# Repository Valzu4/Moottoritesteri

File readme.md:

# Motor tester
This project is a motor tester for testing vending machine motors for various different fault types.

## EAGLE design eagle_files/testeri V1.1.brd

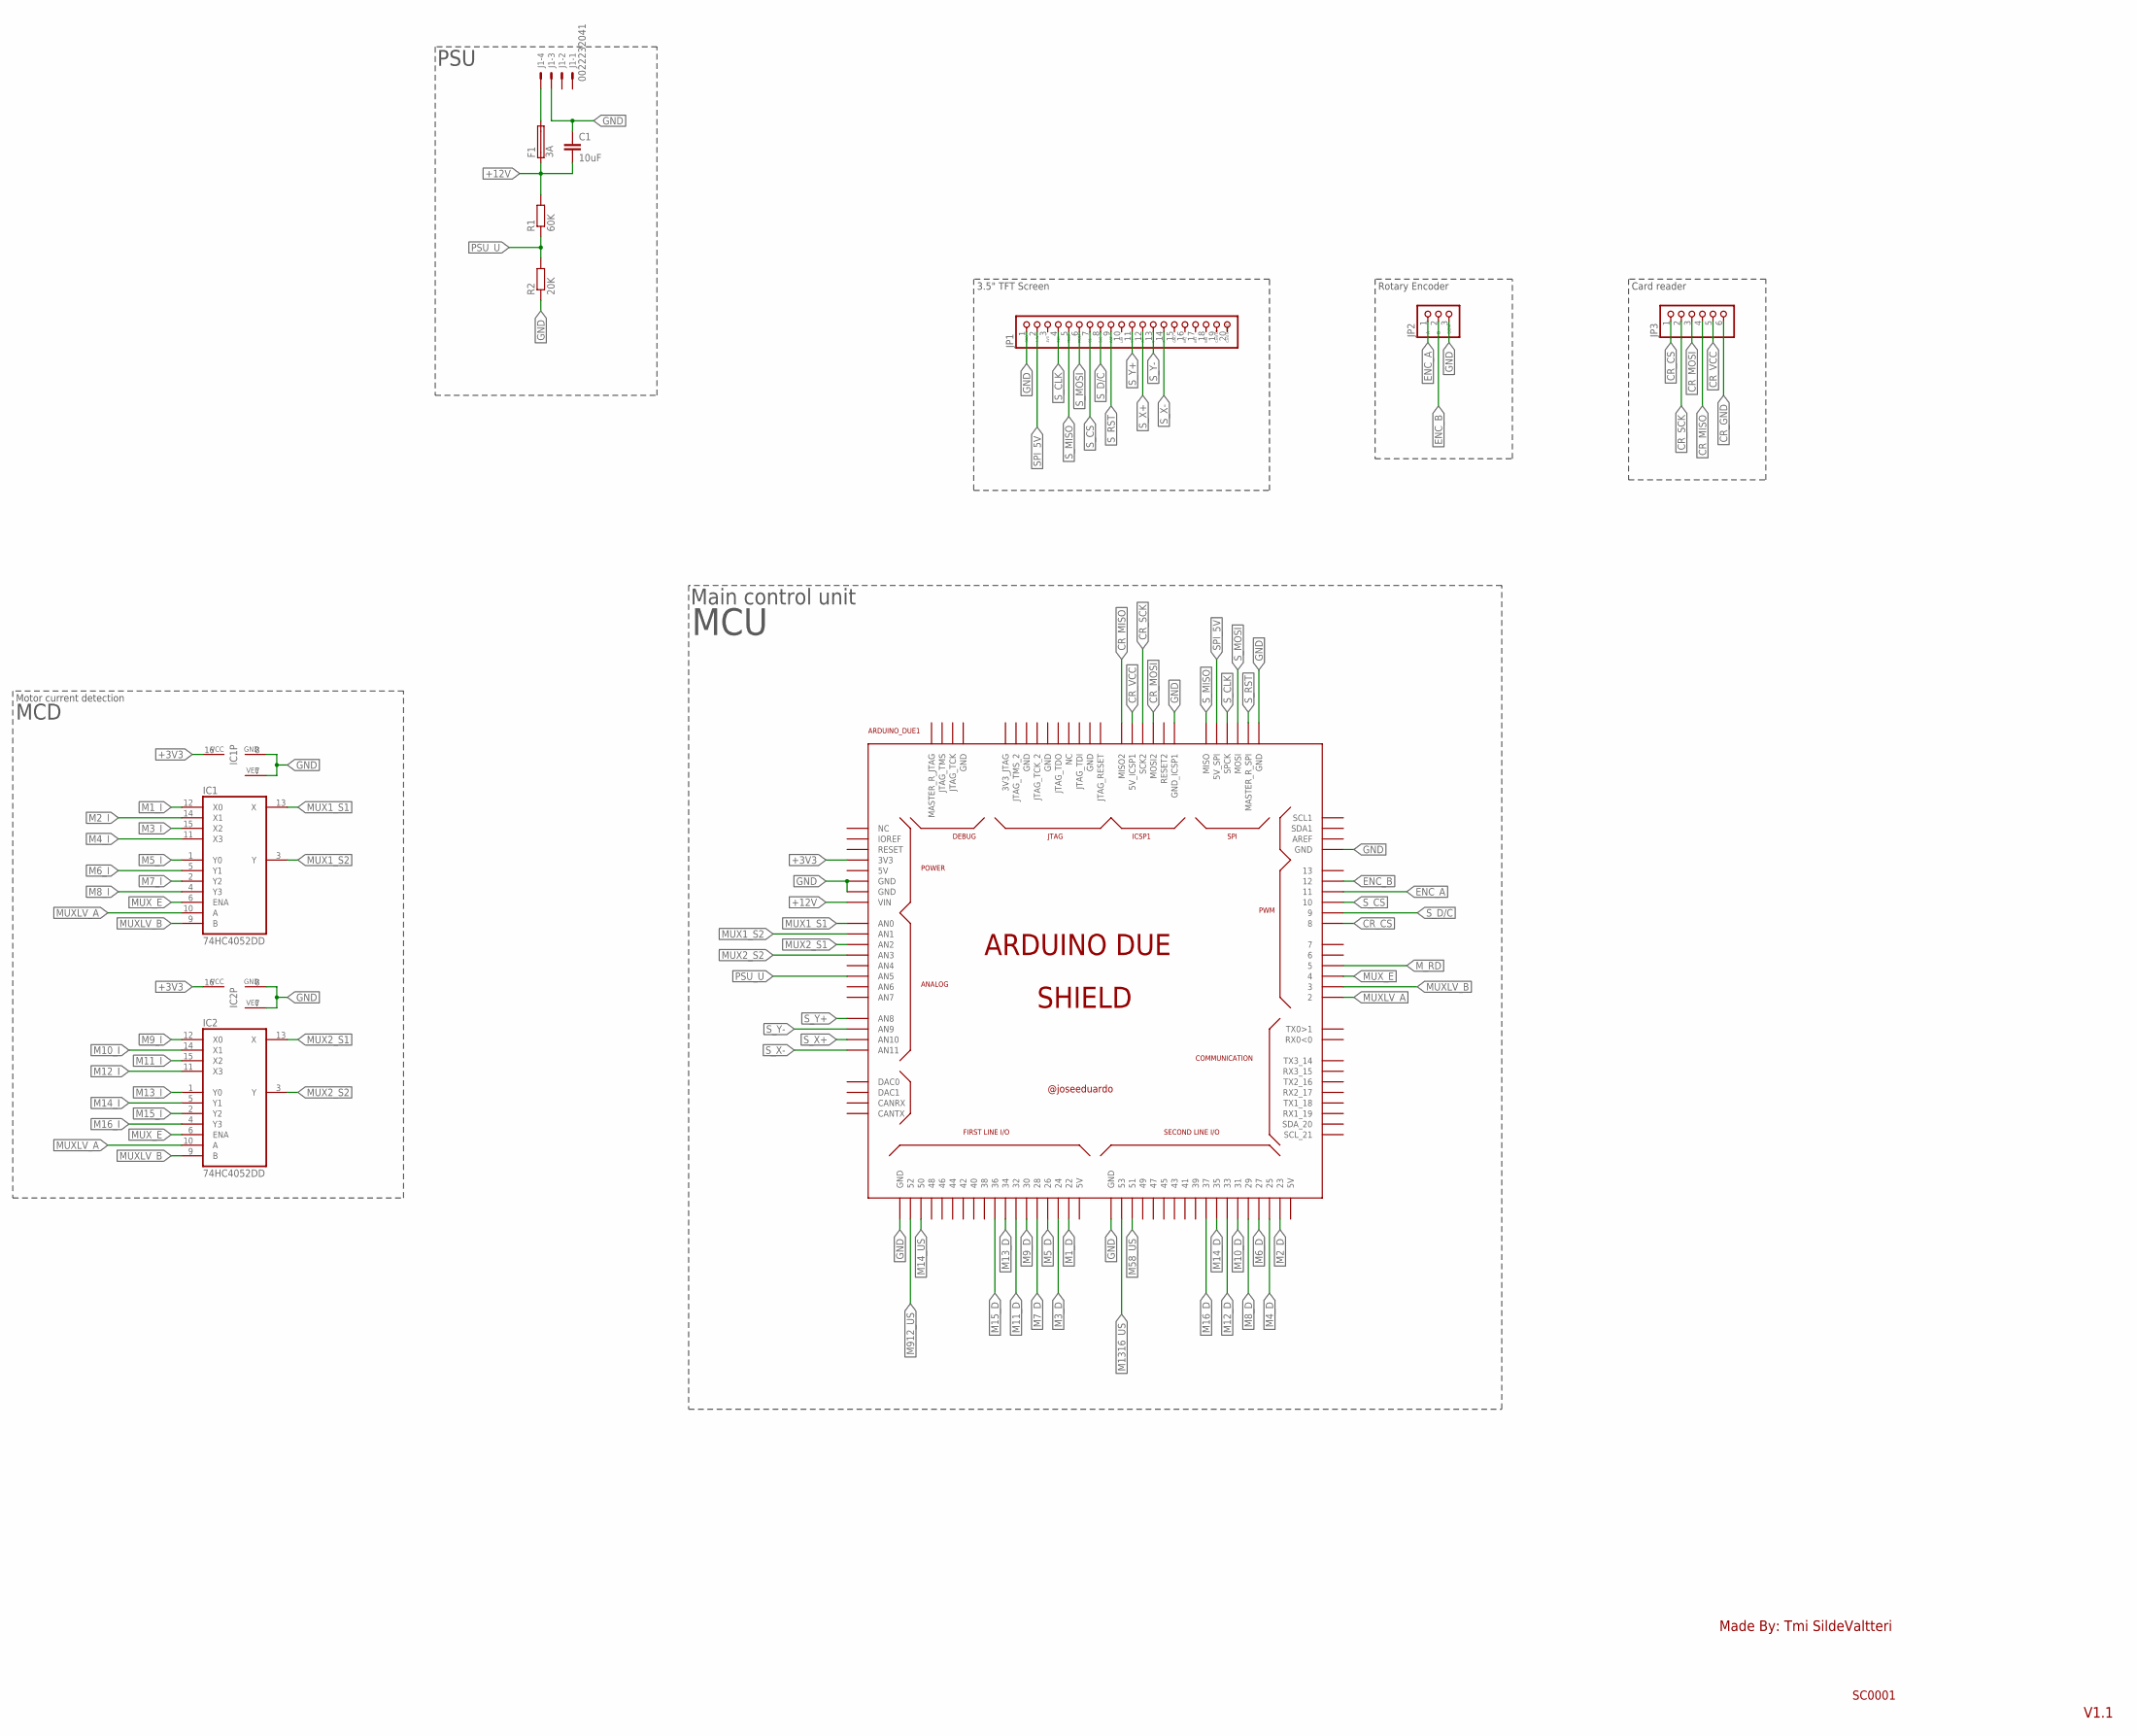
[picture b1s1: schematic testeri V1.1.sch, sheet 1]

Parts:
ARDUINO_DUE1: ARDUINO_DUE_SHIELD
C1: 10uF; C3216
F1: 3A; SH22,5
IC1, IC2: 74HC4052DD; SO16
J1: 0022232041; 6410-04
JP1: PINHD-1X20; 1X20
JP2: PINHD-1X3; 1X03
JP3: PINHD-1X6; 1X06
R1: 60K; R3216W
R2: 20K; R3216W

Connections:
+3V3: ARDUINO_DUE1.3V3, IC1.16 (VCC), IC2.16 (VCC); also elsewhere on the board
+12V: ARDUINO_DUE1.VIN, C1.2, F1.1, R1.2; also elsewhere on the board
CR_CS: ARDUINO_DUE1.8, JP3.1
CR_GND: JP3.6
CR_MISO: ARDUINO_DUE1.MISO2, JP3.4
CR_MOSI: ARDUINO_DUE1.MOSI2, JP3.3
CR_SCK: ARDUINO_DUE1.SCK2, JP3.2
CR_VCC: ARDUINO_DUE1.5V_ICSP1, JP3.5
ENC_A: ARDUINO_DUE1.11, JP2.1
ENC_B: ARDUINO_DUE1.12, JP2.2
GND: ARDUINO_DUE1.GND, ARDUINO_DUE1.GND_1 (GND), ARDUINO_DUE1.GND_2 (GND), ARDUINO_DUE1.GND_3 (GND), ARDUINO_DUE1.GND_4 (GND), ARDUINO_DUE1.GND_5 (GND), ARDUINO_DUE1.GND_ICSP1, C1.1, IC1.7 (VEE), IC1.8 (GND), IC2.7 (VEE), IC2.8 (GND), J1.3, JP1.1, JP2.3, R2.1; also elsewhere on the board
M1_D: ARDUINO_DUE1.22; also elsewhere on the board
M1_I: IC1.12 (X0); also elsewhere on the board
M2_D: ARDUINO_DUE1.23; also elsewhere on the board
M2_I: IC1.14 (X1); also elsewhere on the board
M3_D: ARDUINO_DUE1.24; also elsewhere on the board
M3_I: IC1.15 (X2); also elsewhere on the board
M4_D: ARDUINO_DUE1.25; also elsewhere on the board
M4_I: IC1.11 (X3); also elsewhere on the board
M5_D: ARDUINO_DUE1.26; also elsewhere on the board
M5_I: IC1.1 (Y0); also elsewhere on the board
M6_D: ARDUINO_DUE1.27; also elsewhere on the board
M6_I: IC1.5 (Y1); also elsewhere on the board
M7_D: ARDUINO_DUE1.28; also elsewhere on the board
M7_I: IC1.2 (Y2); also elsewhere on the board
M8_D: ARDUINO_DUE1.29; also elsewhere on the board
M8_I: IC1.4 (Y3); also elsewhere on the board
M9_D: ARDUINO_DUE1.30; also elsewhere on the board
M9_I: IC2.12 (X0); also elsewhere on the board
M10_D: ARDUINO_DUE1.31; also elsewhere on the board
M10_I: IC2.14 (X1); also elsewhere on the board
M11_D: ARDUINO_DUE1.32; also elsewhere on the board
M11_I: IC2.15 (X2); also elsewhere on the board
M12_D: ARDUINO_DUE1.33; also elsewhere on the board
M12_I: IC2.11 (X3); also elsewhere on the board
M13_D: ARDUINO_DUE1.34; also elsewhere on the board
M13_I: IC2.1 (Y0); also elsewhere on the board
M14_D: ARDUINO_DUE1.35; also elsewhere on the board
M14_I: IC2.5 (Y1); also elsewhere on the board
M14_US: ARDUINO_DUE1.50; also elsewhere on the board
M15_D: ARDUINO_DUE1.36; also elsewhere on the board
M15_I: IC2.2 (Y2); also elsewhere on the board
M16_D: ARDUINO_DUE1.37; also elsewhere on the board
M16_I: IC2.4 (Y3); also elsewhere on the board
M58_US: ARDUINO_DUE1.51; also elsewhere on the board
M912_US: ARDUINO_DUE1.52; also elsewhere on the board
M1316_US: ARDUINO_DUE1.53; also elsewhere on the board
MUX1_S1: ARDUINO_DUE1.A0 (AN0), IC1.13 (X)
MUX1_S2: ARDUINO_DUE1.A1 (AN1), IC1.3 (Y)
MUX2_S1: ARDUINO_DUE1.A2 (AN2), IC2.13 (X)
MUX2_S2: ARDUINO_DUE1.A3 (AN3), IC2.3 (Y)
MUXLV_A: ARDUINO_DUE1.2, IC1.10 (A), IC2.10 (A)
MUXLV_B: ARDUINO_DUE1.3, IC1.9 (B), IC2.9 (B)
MUX_E: ARDUINO_DUE1.4, IC1.6 (ENA), IC2.6 (ENA)
M_RD: ARDUINO_DUE1.5; also elsewhere on the board
unnamed: F1.2, J1.4
PSU_U: ARDUINO_DUE1.A5 (AN5), R1.1, R2.2
SPI_5V: ARDUINO_DUE1.5V_2 (5V_SPI), JP1.2
S_CLK: ARDUINO_DUE1.SPCK, JP1.4
S_CS: ARDUINO_DUE1.10, JP1.7
S_D/C: ARDUINO_DUE1.9, JP1.8
S_MISO: ARDUINO_DUE1.MISO, JP1.5
S_MOSI: ARDUINO_DUE1.MOSI, JP1.6
S_RST: ARDUINO_DUE1.MASTER_RESET_SPI (MASTER_R_SPI), JP1.9
S_X+: ARDUINO_DUE1.A10 (AN10), JP1.12
S_X-: ARDUINO_DUE1.A11 (AN11), JP1.14
S_Y+: ARDUINO_DUE1.A8 (AN8), JP1.11
S_Y-: ARDUINO_DUE1.A9 (AN9), JP1.13

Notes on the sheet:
Made By: Tmi SildeValtteri
SC0001
V1.1
COM
Rotary Encoder
3.5" TFT Screen
PSU
Motor current detection
Main control unit
MCU
MCD
Card reader

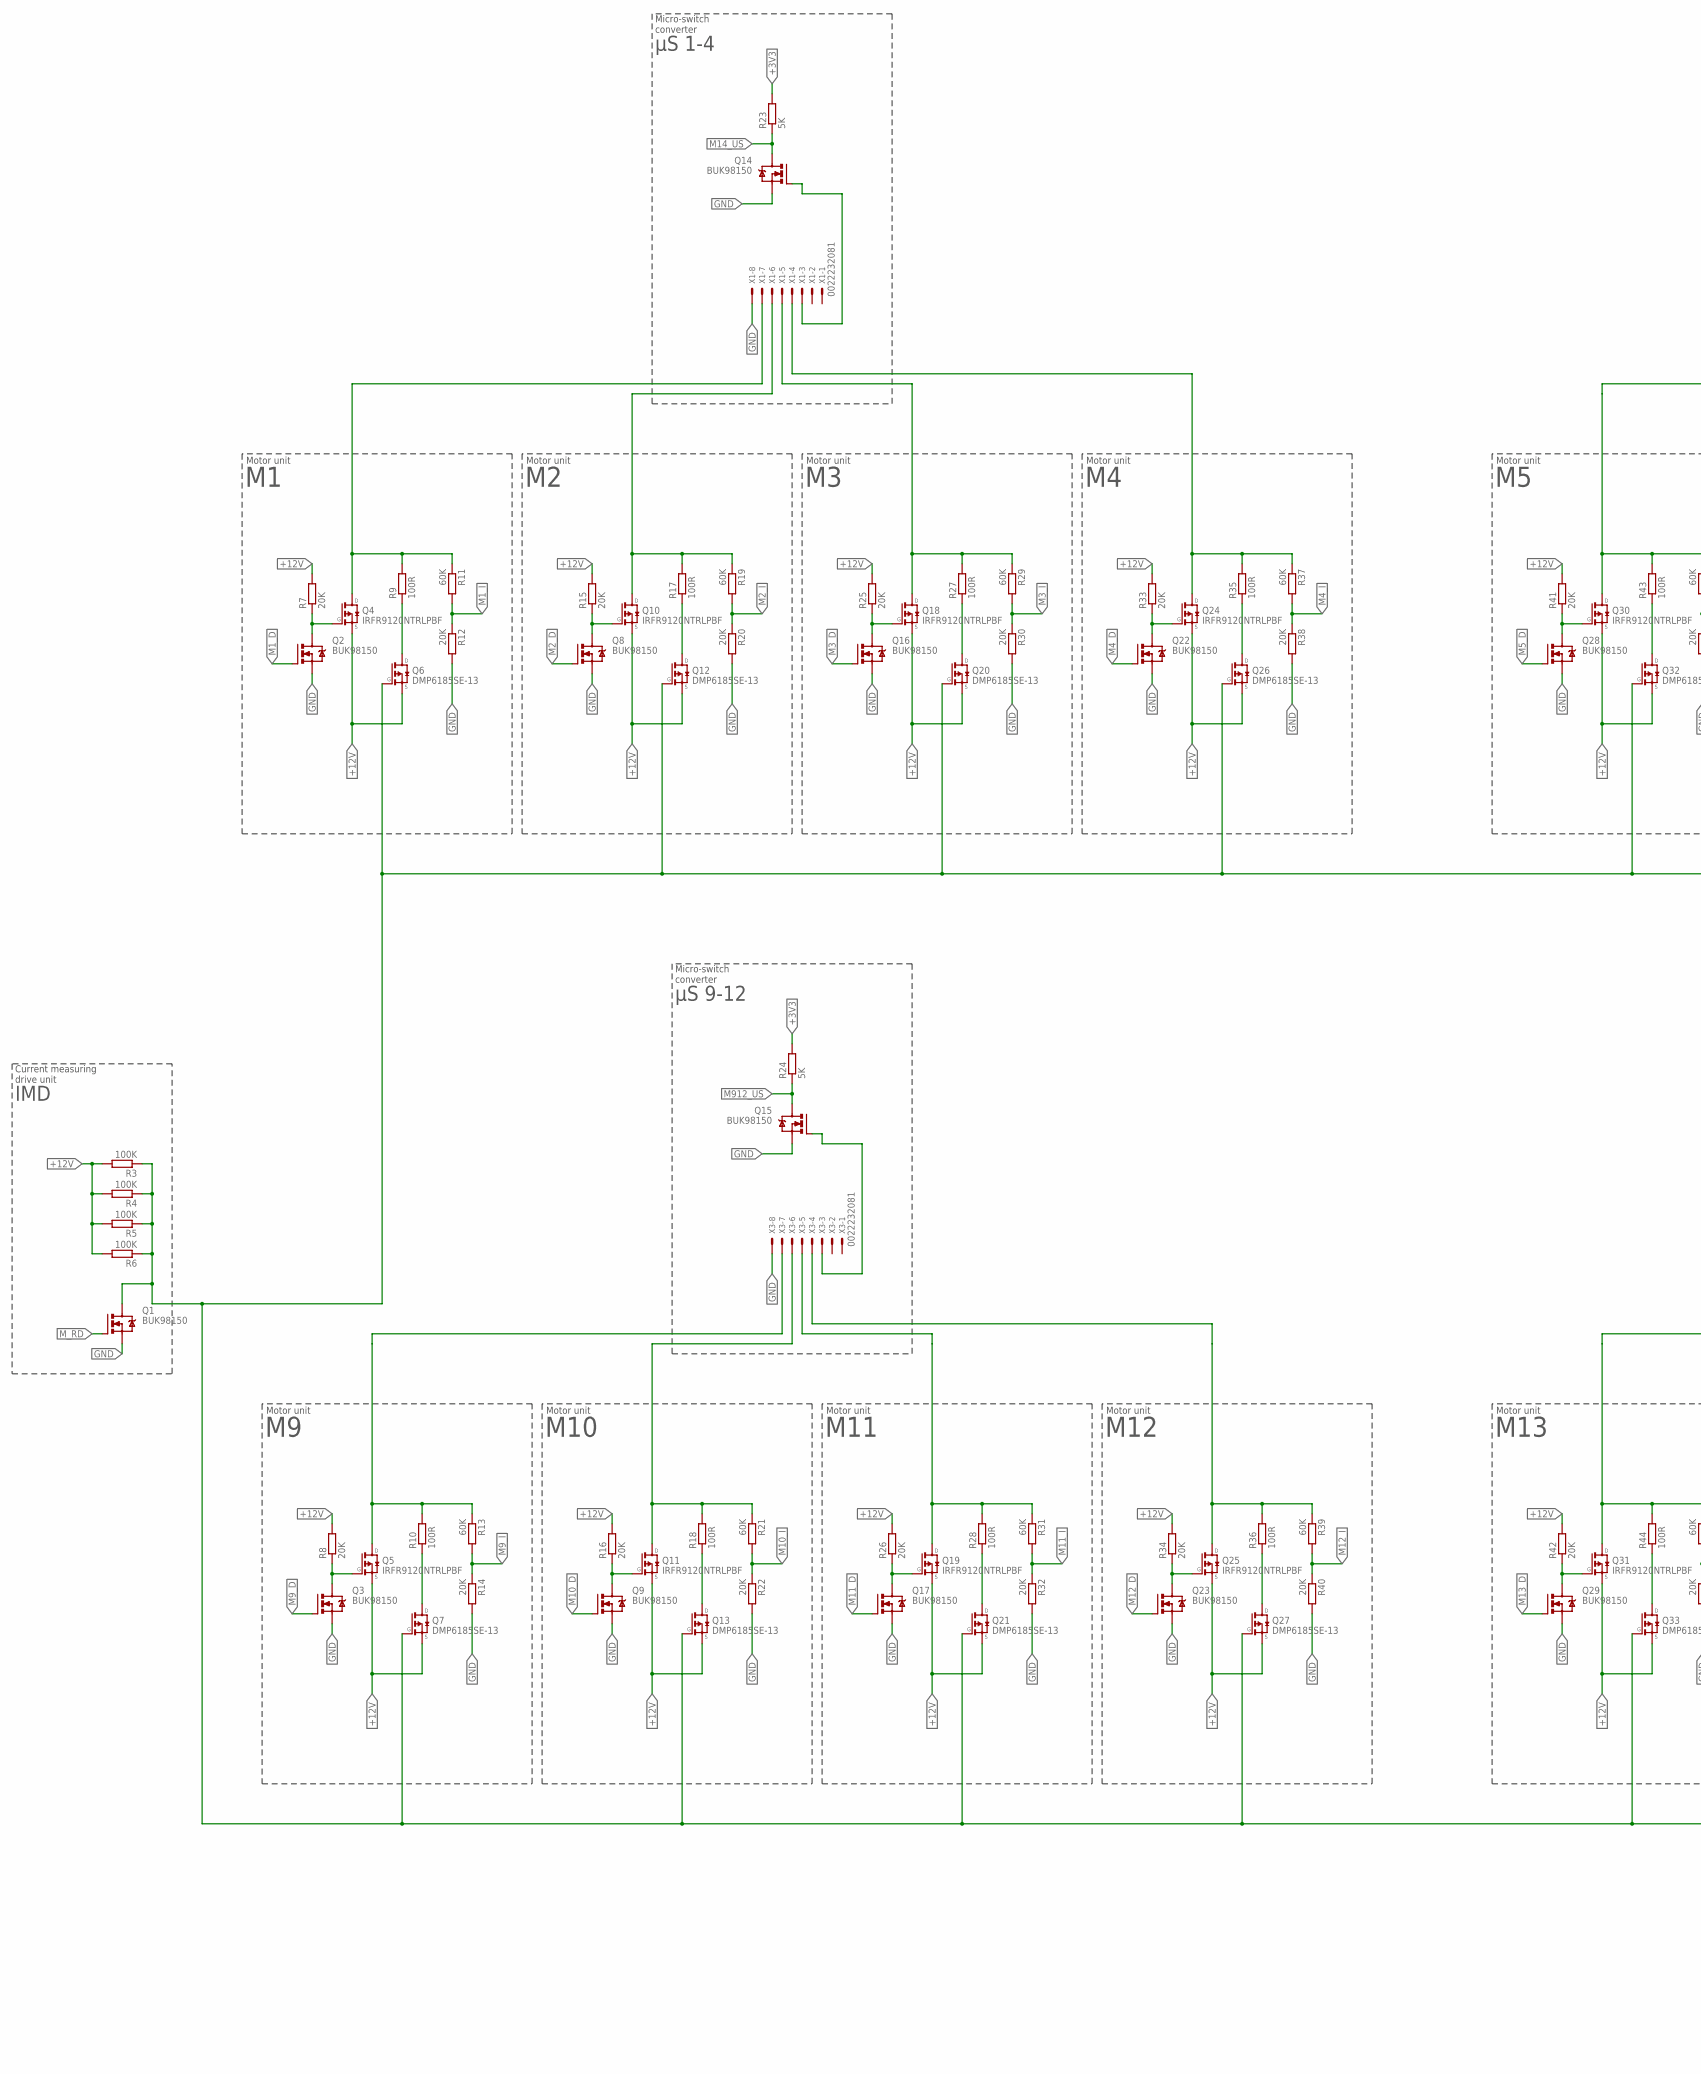
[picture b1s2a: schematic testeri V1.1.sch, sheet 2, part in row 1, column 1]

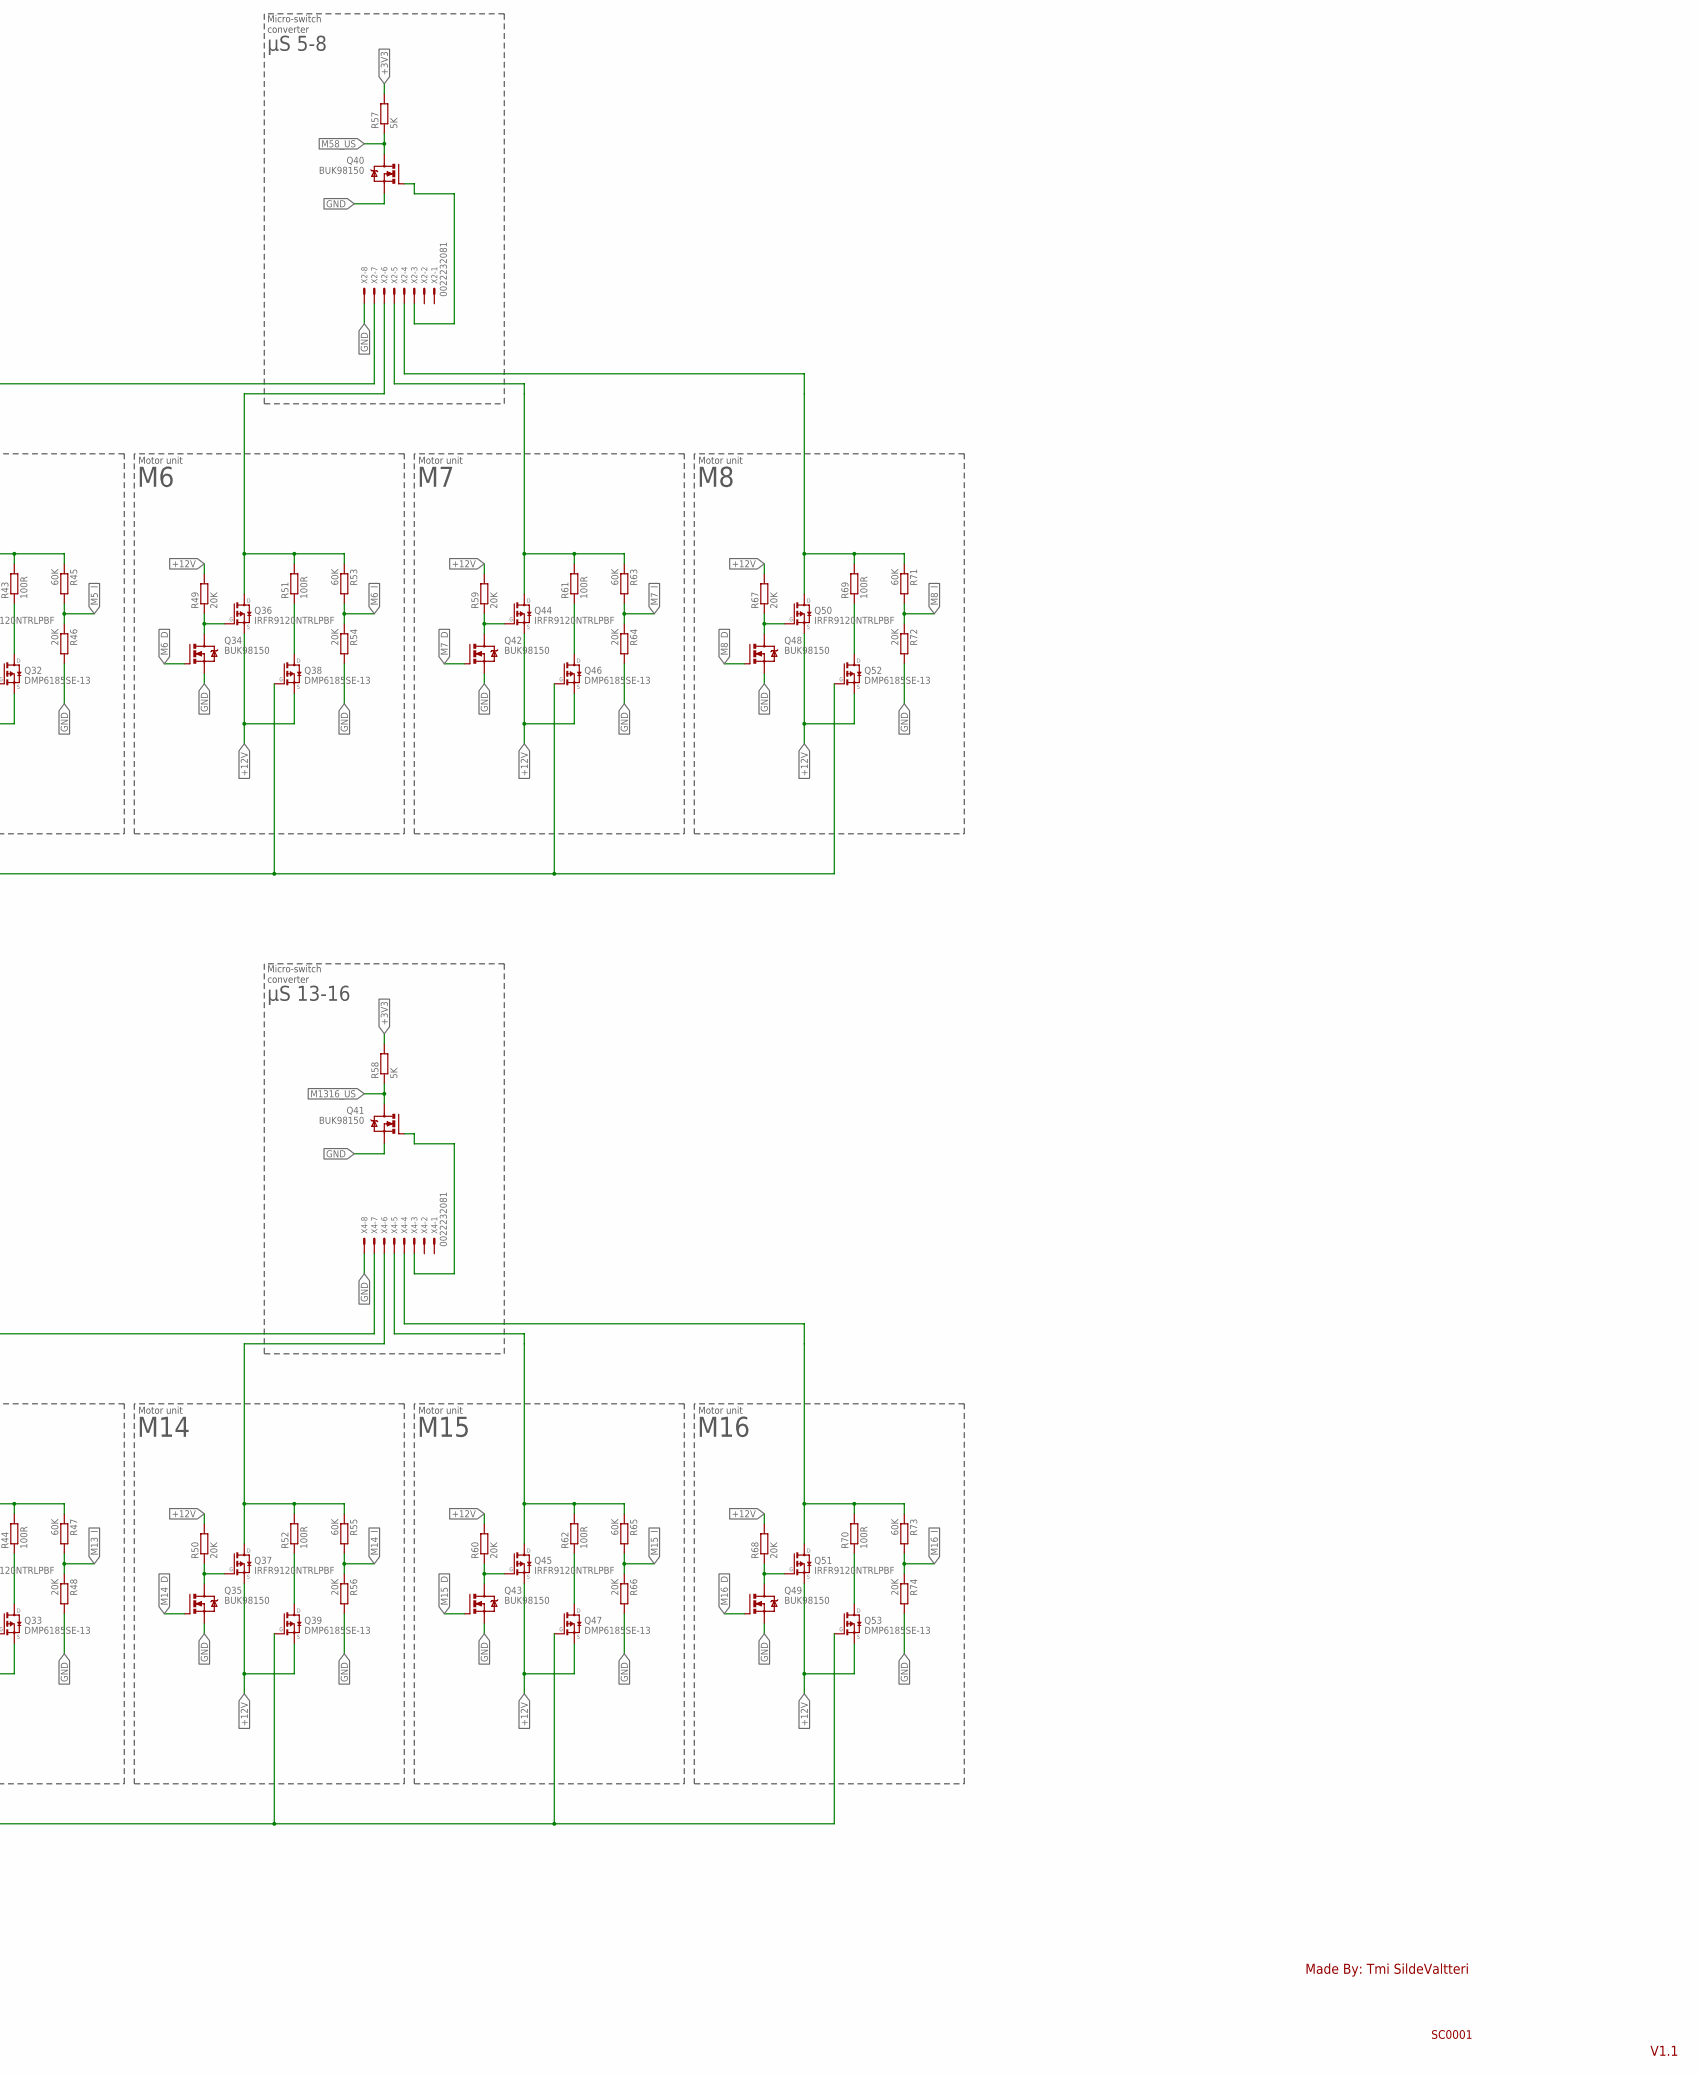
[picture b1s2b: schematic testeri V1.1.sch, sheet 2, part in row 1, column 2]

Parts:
Q1, Q2, Q3, Q8, Q9, Q14, Q15, Q16, Q17, Q22, Q23, Q28, Q29, Q34, Q35, Q40, Q41, Q42, Q43, Q48, Q49: BUK98150; SOT223
Q4, Q5, Q10, Q11, Q18, Q19, Q24, Q25, Q30, Q31, Q36, Q37, Q44, Q45, Q50, Q51: IRFR9120NTRLPBF; D-PAK_TO252AA
Q6, Q7, Q12, Q13, Q20, Q21, Q26, Q27, Q32, Q33, Q38, Q39, Q46, Q47, Q52, Q53: DMP6185SE-13; SOT223
R3, R4, R5, R6: 100K; R3216W
R7, R8, R12, R14, R15, R16, R20, R22, R25, R26, R30, R32, R33, R34, R38, R40, R41, R42, R46, R48, R49, R50, R54, R56, R59, R60, R64, R66, R67, R68, R72, R74: 20K; R3216W
R9, R10, R17, R18, R27, R28, R35, R36, R43, R44, R51, R52, R61, R62, R69, R70: 100R; 0411/15
R11, R13, R19, R21, R29, R31, R37, R39, R45, R47, R53, R55, R63, R65, R71, R73: 60K; R3216W
R23, R24, R57, R58: 5K; R3216W
X1, X2, X3, X4: 0022232081; 22-23-2081

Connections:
+3V3: R23.2, R24.2, R57.2, R58.2; also elsewhere on the board
+12V: Q4.3 (S), Q5.3 (S), Q6.3 (S), Q7.3 (S), Q10.3 (S), Q11.3 (S), Q12.3 (S), Q13.3 (S), Q18.3 (S), Q19.3 (S), Q20.3 (S), Q21.3 (S), Q24.3 (S), Q25.3 (S), Q26.3 (S), Q27.3 (S), Q30.3 (S), Q31.3 (S), Q32.3 (S), Q33.3 (S), Q36.3 (S), Q37.3 (S), Q38.3 (S), Q39.3 (S), Q44.3 (S), Q45.3 (S), Q46.3 (S), Q47.3 (S), Q50.3 (S), Q51.3 (S), Q52.3 (S), Q53.3 (S), R3.2, R4.2, R5.2, R6.2, R7.2, R8.2, R15.2, R16.2, R25.2, R26.2, R33.2, R34.2, R41.2, R42.2, R49.2, R50.2, R59.2, R60.2, R67.2, R68.2; also elsewhere on the board
GND: Q1.3 (S), Q2.3 (S), Q3.3 (S), Q8.3 (S), Q9.3 (S), Q14.3 (S), Q15.3 (S), Q16.3 (S), Q17.3 (S), Q22.3 (S), Q23.3 (S), Q28.3 (S), Q29.3 (S), Q34.3 (S), Q35.3 (S), Q40.3 (S), Q41.3 (S), Q42.3 (S), Q43.3 (S), Q48.3 (S), Q49.3 (S), R12.2, R14.2, R20.2, R22.2, R30.2, R32.2, R38.2, R40.2, R46.2, R48.2, R54.2, R56.2, R64.2, R66.2, R72.2, R74.2, X1.8, X2.8, X3.8, X4.8; also elsewhere on the board
M1_D: Q2.1 (G); also elsewhere on the board
M1_I: R11.2, R12.1; also elsewhere on the board
M2_D: Q8.1 (G); also elsewhere on the board
M2_I: R19.2, R20.1; also elsewhere on the board
M3_D: Q16.1 (G); also elsewhere on the board
M3_I: R29.2, R30.1; also elsewhere on the board
M4_D: Q22.1 (G); also elsewhere on the board
M4_I: R37.2, R38.1; also elsewhere on the board
M5_D: Q28.1 (G); also elsewhere on the board
M5_I: R45.2, R46.1; also elsewhere on the board
M6_D: Q34.1 (G); also elsewhere on the board
M6_I: R53.2, R54.1; also elsewhere on the board
M7_D: Q42.1 (G); also elsewhere on the board
M7_I: R63.2, R64.1; also elsewhere on the board
M8_D: Q48.1 (G); also elsewhere on the board
M8_I: R71.2, R72.1; also elsewhere on the board
M9_D: Q3.1 (G); also elsewhere on the board
M9_I: R13.2, R14.1; also elsewhere on the board
M10_D: Q9.1 (G); also elsewhere on the board
M10_I: R21.2, R22.1; also elsewhere on the board
M11_D: Q17.1 (G); also elsewhere on the board
M11_I: R31.2, R32.1; also elsewhere on the board
M12_D: Q23.1 (G); also elsewhere on the board
M12_I: R39.2, R40.1; also elsewhere on the board
M13_D: Q29.1 (G); also elsewhere on the board
M13_I: R47.2, R48.1; also elsewhere on the board
M14_D: Q35.1 (G); also elsewhere on the board
M14_I: R55.2, R56.1; also elsewhere on the board
M14_US: Q14.2 (D), Q14.4 (D), R23.1; also elsewhere on the board
M15_D: Q43.1 (G); also elsewhere on the board
M15_I: R65.2, R66.1; also elsewhere on the board
M16_D: Q49.1 (G); also elsewhere on the board
M16_I: R73.2, R74.1; also elsewhere on the board
M58_US: Q40.2 (D), Q40.4 (D), R57.1; also elsewhere on the board
M912_US: Q15.2 (D), Q15.4 (D), R24.1; also elsewhere on the board
M1316_US: Q41.2 (D), Q41.4 (D), R58.1; also elsewhere on the board
M_RD: Q1.1 (G); also elsewhere on the board
unnamed: Q8.2 (D), Q8.4 (D), Q10.1 (G), R15.1
unnamed: Q14.1 (G), X1.3
unnamed: Q10.4 (D), R17.2, R19.1, X1.6
unnamed: Q1.2 (D), Q1.4 (D), Q6.1 (G), Q7.1 (G), Q12.1 (G), Q13.1 (G), Q20.1 (G), Q21.1 (G), Q26.1 (G), Q27.1 (G), Q32.1 (G), Q33.1 (G), Q38.1 (G), Q39.1 (G), Q46.1 (G), Q47.1 (G), Q52.1 (G), Q53.1 (G), R3.1, R4.1, R5.1, R6.1
unnamed: Q2.2 (D), Q2.4 (D), Q4.1 (G), R7.1
unnamed: Q4.4 (D), R9.2, R11.1, X1.7
unnamed: Q6.2 (D), Q6.4 (D), R9.1
unnamed: Q12.2 (D), Q12.4 (D), R17.1
unnamed: Q40.1 (G), X2.3
unnamed: Q16.2 (D), Q16.4 (D), Q18.1 (G), R25.1
unnamed: Q18.4 (D), R27.2, R29.1, X1.5
unnamed: Q20.2 (D), Q20.4 (D), R27.1
unnamed: Q30.4 (D), R43.2, R45.1, X2.7
unnamed: Q22.2 (D), Q22.4 (D), Q24.1 (G), R33.1
unnamed: Q26.2 (D), Q26.4 (D), R35.1
unnamed: Q36.4 (D), R51.2, R53.1, X2.6
unnamed: Q28.2 (D), Q28.4 (D), Q30.1 (G), R41.1
unnamed: Q3.2 (D), Q3.4 (D), Q5.1 (G), R8.1
unnamed: Q32.2 (D), Q32.4 (D), R43.1
unnamed: Q44.4 (D), R61.2, R63.1, X2.5
unnamed: Q34.2 (D), Q34.4 (D), Q36.1 (G), R49.1
unnamed: Q7.2 (D), Q7.4 (D), R10.1
unnamed: Q38.2 (D), Q38.4 (D), R51.1
unnamed: Q50.4 (D), R69.2, R71.1, X2.4
unnamed: Q42.2 (D), Q42.4 (D), Q44.1 (G), R59.1
unnamed: Q9.2 (D), Q9.4 (D), Q11.1 (G), R16.1
unnamed: Q46.2 (D), Q46.4 (D), R61.1
unnamed: Q24.4 (D), R35.2, R37.1, X1.4
unnamed: Q48.2 (D), Q48.4 (D), Q50.1 (G), R67.1
unnamed: Q13.2 (D), Q13.4 (D), R18.1
unnamed: Q52.2 (D), Q52.4 (D), R69.1
unnamed: Q17.2 (D), Q17.4 (D), Q19.1 (G), R26.1
unnamed: Q21.2 (D), Q21.4 (D), R28.1
unnamed: Q23.2 (D), Q23.4 (D), Q25.1 (G), R34.1
unnamed: Q27.2 (D), Q27.4 (D), R36.1
unnamed: Q15.1 (G), X3.3
unnamed: Q5.4 (D), R10.2, R13.1, X3.7
unnamed: Q11.4 (D), R18.2, R21.1, X3.6
unnamed: Q19.4 (D), R28.2, R31.1, X3.5
unnamed: Q25.4 (D), R36.2, R39.1, X3.4
unnamed: Q29.2 (D), Q29.4 (D), Q31.1 (G), R42.1
unnamed: Q33.2 (D), Q33.4 (D), R44.1
unnamed: Q35.2 (D), Q35.4 (D), Q37.1 (G), R50.1
unnamed: Q39.2 (D), Q39.4 (D), R52.1
unnamed: Q43.2 (D), Q43.4 (D), Q45.1 (G), R60.1
unnamed: Q47.2 (D), Q47.4 (D), R62.1
unnamed: Q49.2 (D), Q49.4 (D), Q51.1 (G), R68.1
unnamed: Q53.2 (D), Q53.4 (D), R70.1
unnamed: Q41.1 (G), X4.3
unnamed: Q31.4 (D), R44.2, R47.1, X4.7
unnamed: Q37.4 (D), R52.2, R55.1, X4.6
unnamed: Q45.4 (D), R62.2, R65.1, X4.5
unnamed: Q51.4 (D), R70.2, R73.1, X4.4

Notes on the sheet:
Made By: Tmi SildeValtteri
SC0001
V1.1
Motor unit
Current measuring drive unit
Micro-switch converter
M10
M11
M12
M13
M14
M15
M16
µS 1-4
µS 5-8
µS 9-12
µS 13-16
IMD

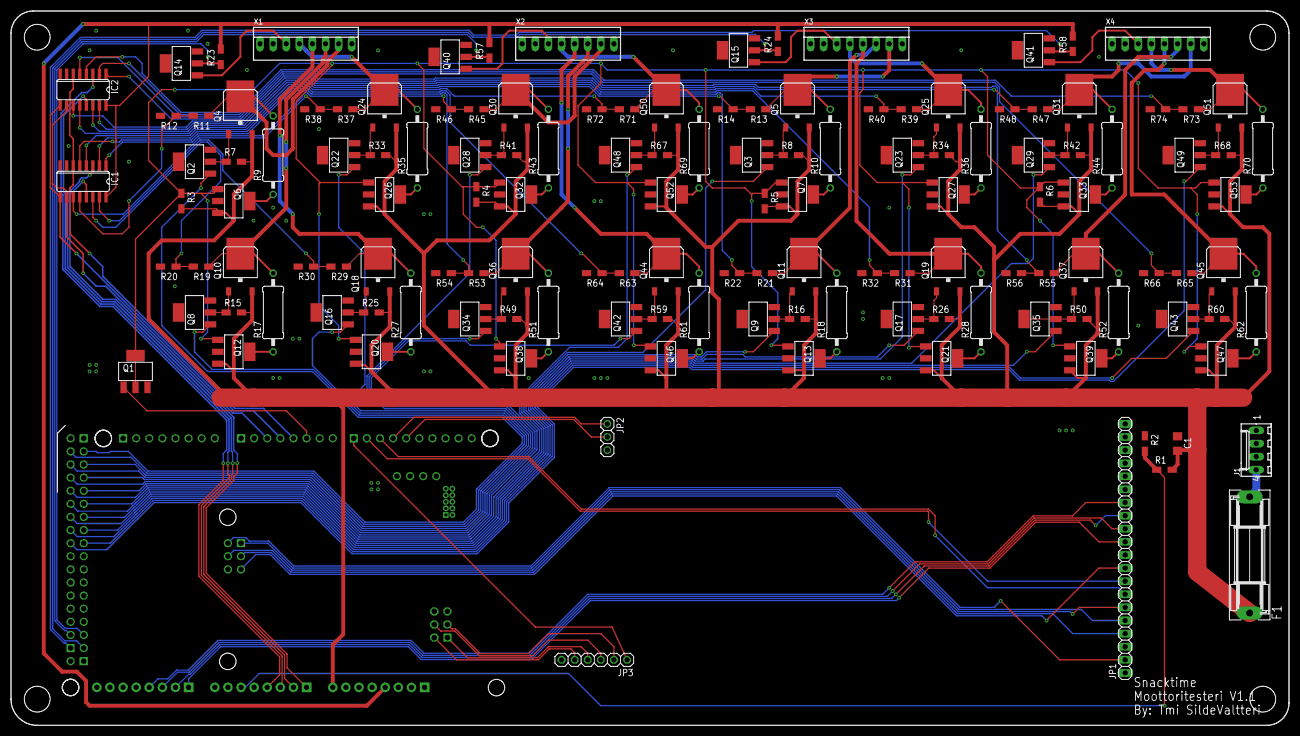
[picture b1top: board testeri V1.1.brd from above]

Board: 2 copper layers, 247.7 x 138.4 mm, 140 parts (1 on the bottom side), 120 nets.

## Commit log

2024-01-27 Changes to files
2024-01-27 Added pdf files
2024-01-27 Changes to folder names
